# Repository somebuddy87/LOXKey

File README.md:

LOXKey

Es handelt sich hierbei um ein Testprogramm um die Funktion der LOXKey! Platine zu überprüfen.

https://unser-smartes-zuhause.de

https://unser-smartes-zuhause.de/2021/05/30/loxkey-unser-smartes-schluesselbrett-2/

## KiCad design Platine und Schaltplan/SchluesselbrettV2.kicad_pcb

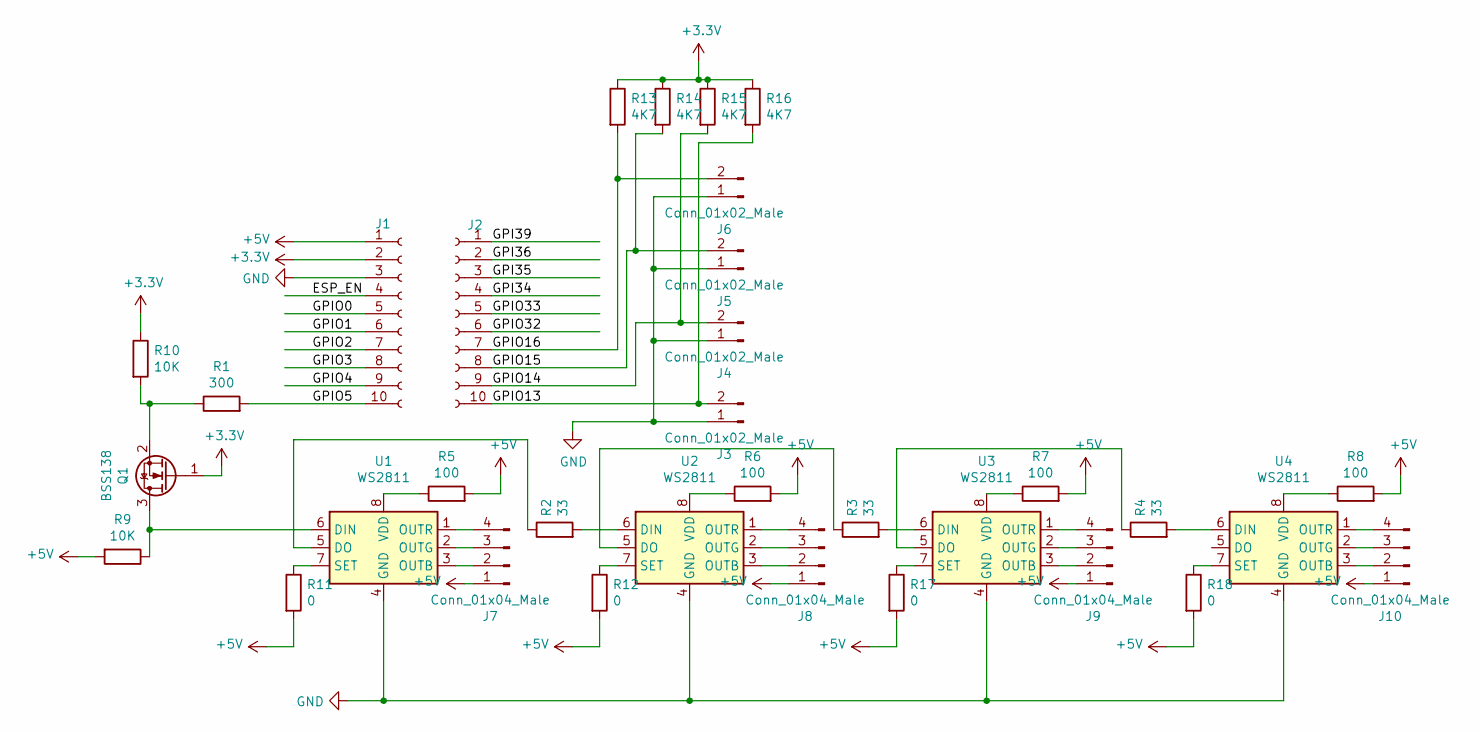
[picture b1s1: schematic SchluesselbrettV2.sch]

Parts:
J1, J2: Conn_01x10_Female; PinSocket_1x10_P2.54mm_Vertical
J3, J4, J5, J6: Conn_01x02_Male; JST_XH_S2B-XH-A_1x02_P2.50mm_Horizontal
J7, J8, J9, J10: Conn_01x04_Male; JST_XH_S4B-XH-A_1x04_P2.50mm_Horizontal
Q1: BSS138; SOT-23
R1: 300; R_0805_2012Metric
R2, R3, R4: 33; R_0805_2012Metric
R5, R6, R7, R8: 100; R_0805_2012Metric
R9, R10: 10K; R_0805_2012Metric
R11, R12, R17, R18: 0; R_0805_2012Metric
R13, R14, R15, R16: 4K7; R_0805_2012Metric
U1, U2, U3, U4: WS2811; SOIC-8_3.9x4.9mm_P1.27mm

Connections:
+3V3: J1.2, Q1.1 (G), R10.1, R13.1, R14.1, R15.1, R16.1
+5V: J1.1, J7.1, J8.1, J9.1, J10.1, R5.2, R6.2, R7.2, R8.2, R9.2, R11.2, R12.2, R17.2, R18.2
/ESP_EN: J1.4
/GPI34: J2.4
/GPI35: J2.3
/GPI36: J2.2
/GPI39: J2.1
/GPIO0: J1.5
/GPIO1: J1.6
/GPIO2: J1.7
/GPIO3: J1.8
/GPIO4: J1.9
/GPIO5: J1.10, R1.2
/GPIO13: J2.10, J3.2, R16.2
/GPIO14: J2.9, J4.2, R15.2
/GPIO15: J2.8, J5.2, R14.2
/GPIO16: J2.7, J6.2, R13.2
/GPIO32: J2.6
/GPIO33: J2.5
GND: J1.3, J3.1, J4.1, J5.1, J6.1, U1.4 (GND), U2.4 (GND), U3.4 (GND), U4.4 (GND)
unnamed: J7.2, U1.3 (OUTB)
unnamed: J7.3, U1.2 (OUTG)
unnamed: J7.4, U1.1 (OUTR)
unnamed: J8.2, U2.3 (OUTB)
unnamed: J8.3, U2.2 (OUTG)
unnamed: J8.4, U2.1 (OUTR)
unnamed: J9.2, U3.3 (OUTB)
unnamed: J9.3, U3.2 (OUTG)
unnamed: J9.4, U3.1 (OUTR)
unnamed: J10.2, U4.3 (OUTB)
unnamed: J10.3, U4.2 (OUTG)
unnamed: J10.4, U4.1 (OUTR)
unnamed: Q1.2 (S), R1.1, R10.2
unnamed: Q1.3 (D), R9.1, U1.6 (DIN)
unnamed: R2.1, U1.5 (DO)
unnamed: R2.2, U2.6 (DIN)
unnamed: R3.1, U2.5 (DO)
unnamed: R3.2, U3.6 (DIN)
unnamed: R4.1, U3.5 (DO)
unnamed: R4.2, U4.6 (DIN)
unnamed: R5.1, U1.8 (VDD)
unnamed: R6.1, U2.8 (VDD)
unnamed: R7.1, U3.8 (VDD)
unnamed: R8.1, U4.8 (VDD)
unnamed: R11.1, U1.7 (SET)
unnamed: R12.1, U2.7 (SET)
unnamed: R17.1, U3.7 (SET)
unnamed: R18.1, U4.7 (SET)

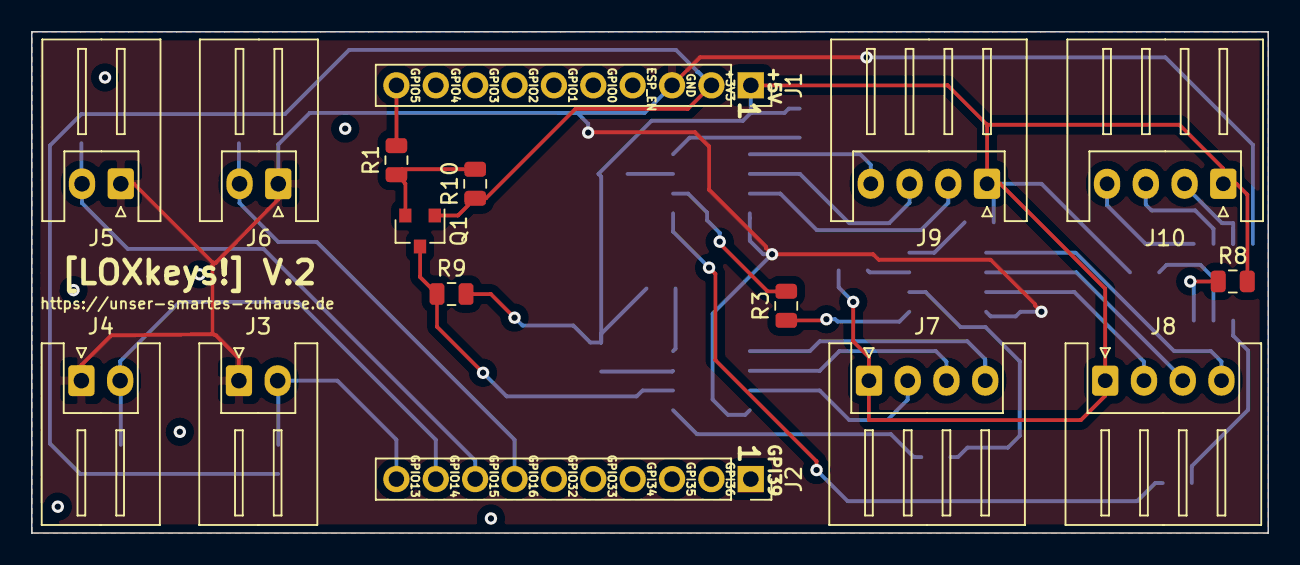
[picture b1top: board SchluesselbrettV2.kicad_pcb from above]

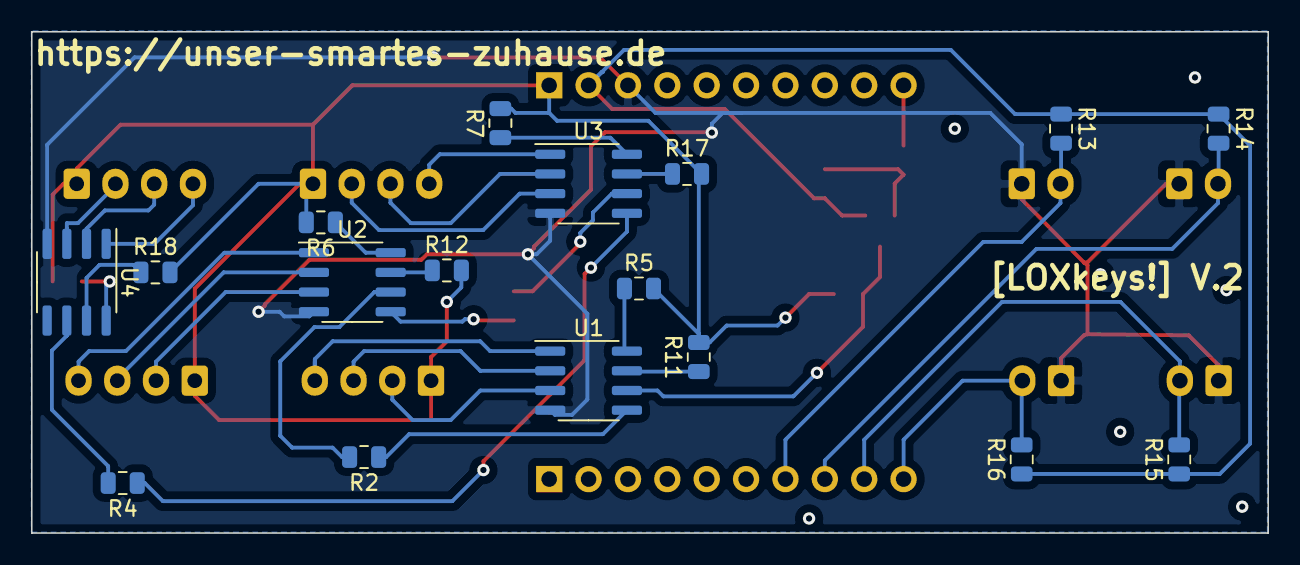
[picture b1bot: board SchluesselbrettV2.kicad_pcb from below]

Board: 2 copper layers, 79.8 x 32.3 mm, 33 parts (17 on the bottom side), 36 nets.

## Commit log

2021-05-30 Initial Upload
2021-05-30 Upload Schaltplan und Layout
